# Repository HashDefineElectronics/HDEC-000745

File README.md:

# HDEC-000745
Robot and image processing developement platform

## Project page
https://www.hashdefineelectronics.com/micro-robot-development-platform-hdec-000745/

## Video
3D printing micro robot chassis (time lapse)

# 1) Initial project setup
When you first clone the project you will need to use the --recursive parameter to clone any of the git submodules used by the project.

`git clone --recursive https://github.com/HashDefineElectronics/HDEC-000745.git`

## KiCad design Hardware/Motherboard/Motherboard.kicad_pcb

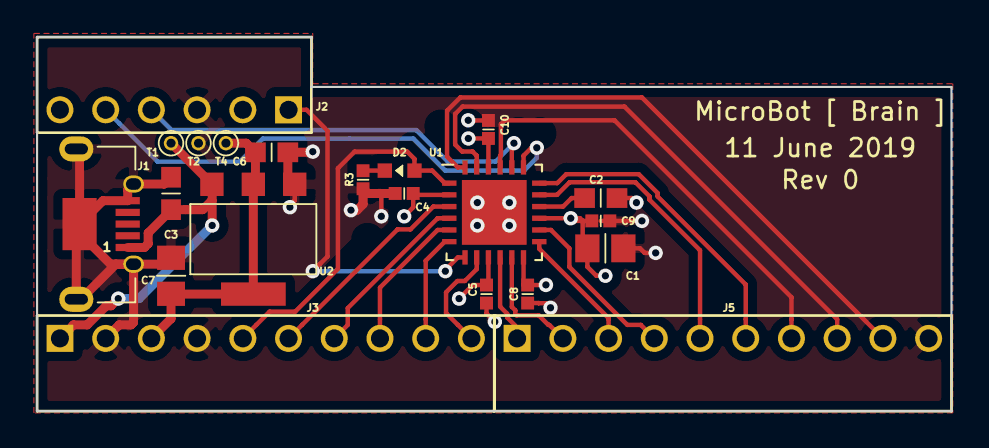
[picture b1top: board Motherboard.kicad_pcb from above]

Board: 4 copper layers, 50.8 x 20.8 mm, 21 parts (0 on the bottom side), 23 nets.

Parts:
C1, C7: C0805C106K8PACTU; CAP_0805
C2: GRM188R71E105KA12D; CAP_0603
C3, C6: C0603C104K4RACTU; CAP_0603
C4, C5, C8, C9, C10: C0402C104K4RACAUTO; CAP_0402
D2: KP-1608SURCK; LED_1.6mmx0.8mm
J1: 47590-0001
J2: 61300611021; 6pin_1row_2.54mm_right_angle
J3, J5: 61301011021; 10pin_1row_2.54mm_right_angle
R3: ERJ2RKF1001X; RES_0402
T1, T2, T4: TEST_PAD; TEST_PAD_0.5mm_Hole
U1: EFM32ZG108F32-QFN24; QFN-24_EP_5x5_Pitch0.65mm
U2: LD1117S33CTR; SOT223

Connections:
+3V3: C1.1, C4.1, C5.1, C6.1, C7.1, C8.1, C9.1, C10.1, J2.2, J3.3, T4.1, U1.2, U1.9, U1.12, U1.15, U1.22, U2.2, U2.4
+5V: C3.1, J1.1, J3.1, T1.1, U2.3
/Micro_P1_LED1: D2.1, J3.5, U1.1
/Micro_P2: J3.6, U1.3
/Micro_P3: J3.7, U1.4
/Micro_P4: J3.8, U1.5
/Micro_P5: J3.9, U1.6
/Micro_P6: J3.10, U1.8
/Micro_P7: J5.1, U1.10
/Micro_P8: J5.2, U1.11
/Micro_P9: J5.3, U1.13
/Micro_P10: J5.4, U1.14
/Micro_P11: J5.5, U1.17
/Micro_P12: J5.6, U1.18
/Micro_P13: J5.7, U1.21
/Micro_P14: J5.8, U1.23
/Micro_P15: J5.9, U1.24
/Micro_SWCLK: J2.5, U1.19
/Micro_SWDIO: J2.4, U1.20
/Micro_~RESET~: J2.1, U1.7
GND: C1.2, C2.2, C3.2, C4.2, C5.2, C6.2, C7.2, C8.2, C9.2, C10.2, J1.5, J1.6, J2.3, J3.2, J3.4, J5.10, R3.2, T2.1, U1.25, U2.1
unnamed: C2.1, U1.16
unnamed: D2.2, R3.1

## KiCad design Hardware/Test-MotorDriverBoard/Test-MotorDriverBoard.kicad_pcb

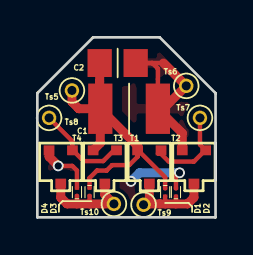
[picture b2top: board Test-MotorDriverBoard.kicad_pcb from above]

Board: 2 copper layers, 9.9 x 10.0 mm, 16 parts (0 on the bottom side), 6 nets.

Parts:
C1: C1210C106K5RACTU; CAP_1210
C2: MC0805B104K500CT; CAP_0805
D1, D2, D3, D4: PMEG1201AESF; SOD962-2
T1, T3: NDS332P; SOT323
T2, T4: PMF370XN,115; SOT323
Ts5, Ts6, Ts7, Ts8, Ts9, Ts10: TEST_PAD; TEST_PAD_0.5mm_Hole

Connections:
+3V3: C1.1, C2.1, D1.1, D3.1, T1.2, T3.2, Ts5.1
/Input_1: T1.1, T2.1, Ts7.1
/Input_2: T3.1, T4.1, Ts8.1
/Motor_A: D1.2, D2.1, T1.3, T2.3, Ts9.1
/Motor_B: D3.2, D4.1, T3.3, T4.3, Ts10.1
GND: C1.2, C2.2, D2.2, D4.2, T2.2, T4.2, Ts6.1

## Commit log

2016-10-04 - added the KiCad Project with the HDE_PUB_LIB - added the mechanical files - added the original altimun design files
2016-10-04 updated the readme file to include the project page and the current video
2016-10-04 fixed the reame text
2016-10-27 - added camera module datasheet - added stm32f429 datasheet - update the HDE_PUB_LIB submodule and Hardware/Motherboard project
2016-10-28 updated hardware/Motherboard/HDE_PUB_LIb library and move it into the Motherboard project root
2016-10-28 updated the motherboard library to fix the components 3d model reference
2016-11-01 reverted the library configuration
2017-09-27 minor commit
2017-09-28 added mosfet library to the project and created the test motor driver board PCB
2017-09-28 created the H-bridge shematic and PCB layout
2017-10-02 updated the library portion of the project
2017-10-02 upated kicad library
2017-10-02 Minor Components changes
2017-10-03 updated KiCad library version to the latest
2017-10-03 minor changes to the motor test board
2018-05-12 added the soft power switch. Will need to be verified.
2018-05-15 Started work on adding the boost converter
2018-05-15 added the current changes from the test motor
2018-05-18 Partial Commit
2019-06-07 Updated schematic and library
2019-06-07 Added the 20way connector and started to layout the main controller
2019-06-11 I've layout the motherboard
